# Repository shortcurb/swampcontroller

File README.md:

# swampcontroller
Hardware and software for controlling evaporative coolers with MQTT and relays

I live in a climate where using evaporative (swamp) coolers to cool dwellings is a generally effective possibility. I have two swamp coolers. I like them because they are cheap to run, cheap and easy to maintain, and if one breaks, I can almost certainly fix it myself, rather than calling a contractor.

My swamp coolers electrical components consist of a water pump and a 1/4HP blower fan with high and low speed settings. I designed this PCB to use an ESP8266 to control three off-board 12V automotive relays, which was easier than trying to figure out how to manage 10A on my little 1oz copper PCB traces.

If anyone is interested, I have 3 remaining unpopulated PCB boards I would be happy to sell/ship somewhere

Hardware features:
* ESP8266 header
* LM2596 (eBay/Amazon THT variant) 4V-40V input
* power header
* 3 relay-control headers

Hardware Problems:
* The pins that control speedheader and fanheader are currently wired to pins that control the flash on an ESP8266. Need to cut the trace and install a jumper wire somewhere else to control them correctly.

Software features:
* State, command, and response MQTT feeds
* State feed publishes the state of the swamper regularly
* Subscribes to command feed to listen for commands
* Response feed is for sending responses to commands
* 5s delay after receiving a command, to prevent changing motor/pump electricity too quickly
Software Problems:
* If the MQTT broker goes down, or Wifi goes down, the device will eventually crash and turn off the blower and fan. This is intended as a purely wifi-controllable device, so its user preference to decide whether failing off is better than failing on. This is kind of an odd edge case, in that my wifi/broker generally only go down if my house electricity goes down, and if my house doesn't have electricity, the swamper isn't running either.

Closing thoughts:
* I assembled the components and relays and a 12V wall wart adapter and cut up some old extension wire and wired everything up in a waterproof junction box and mounted it just below my swamp cooler, powered via an external outlet. Its been working great for the last month!

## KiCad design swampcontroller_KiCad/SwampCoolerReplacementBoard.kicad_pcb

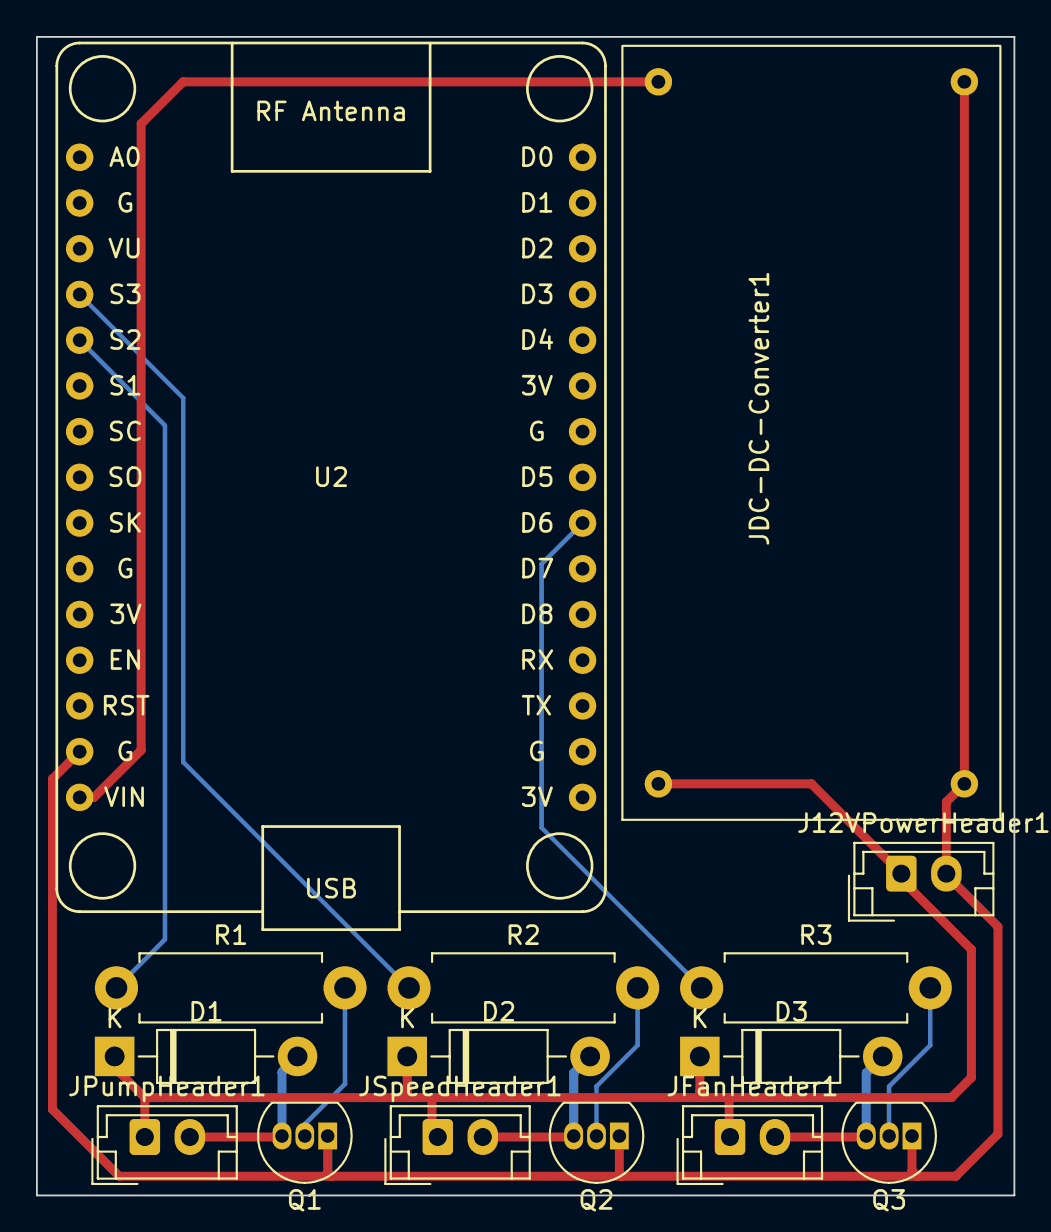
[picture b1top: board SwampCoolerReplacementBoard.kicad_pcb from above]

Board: 2 copper layers, 54.3 x 64.4 mm, 15 parts (0 on the bottom side), 12 nets.

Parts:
D1, D2, D3: 1N4007; D_DO-41_SOD81_P10.16mm_Horizontal
J12VPowerHeader1: Conn_01x02; JST_EH_B2B-EH-A_1x02_P2.50mm_Vertical
JDC-DC-Converter1: Conn_01x04; XL6009E1 DC-DC
JFanHeader1: Conn_01x02; JST_EH_B2B-EH-A_1x02_P2.50mm_Vertical
JPumpHeader1: Conn_01x02; JST_EH_B2B-EH-A_1x02_P2.50mm_Vertical
JSpeedHeader1: Conn_01x02; JST_EH_B2B-EH-A_1x02_P2.50mm_Vertical
Q1, Q2, Q3: 2N7000; TO-92_Inline
R1, R2, R3: 470; R_Axial_DIN0411_L9.9mm_D3.6mm_P12.70mm_Horizontal
U2: NodeMCU1.0(ESP-12E); NodeMCU1.0(12-E)

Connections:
+5V: JDC-DC-Converter1.3, U2.15 (VIN)
+12V: D1.1 (K), D2.1 (K), D3.1 (K), J12VPowerHeader1.1, JDC-DC-Converter1.1, JFanHeader1.1, JPumpHeader1.1, JSpeedHeader1.1
FanRelay: D3.2 (A), JFanHeader1.2, Q3.3 (D)
FanSelect: R2.1, U2.4 (SD3(GPIO10))
FanTrigger: R3.1, U2.22 (D6(GPIO12))
GND: J12VPowerHeader1.2, JDC-DC-Converter1.2, JDC-DC-Converter1.4, Q1.1 (S), Q2.1 (S), Q3.1 (S), U2.14 (GND)
unnamed: Q1.2 (G), R1.2
unnamed: D1.2 (A), JPumpHeader1.2, Q1.3 (D)
unnamed: Q2.2 (G), R2.2
unnamed: Q3.2 (G), R3.2
PumpTrigger: R1.1, U2.5 (SD2(GPIO9))
SpeedRelay: D2.2 (A), JSpeedHeader1.2, Q2.3 (D)

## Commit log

2024-08-18 first hw + sw push
2025-03-28 updated with pcb schematics zip
